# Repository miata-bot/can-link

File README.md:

# Underglow Sync Device

Very much work in progress software and hardware project built with [Kicad](https://www.kicad.org/) for hardware, and C and [Lua](https://www.lua.org) for software. See [The requirements doc](Requirements.md) for the guts of the project.

## TLDR

Here's a [Twitter thread](https://twitter.com/pressy4pie/status/1504309482054029315) showing a demo of the ECU integration.
[video link](https://video.twimg.com/ext_tw_video/1504309386151301125/pu/vid/720x1280/zwIcUEVZBSSQAASE.mp4?tag=12).

Here's a [Twitter thread](https://twitter.com/pressy4pie/status/1506779115122139137) showing a demo of the GPS and companion application. [video link](https://video.twimg.com/ext_tw_video/1506778163891740673/pu/vid/720x1630/oxYdaMkSowD5uJmU.mp4?tag=12).

I've written up a few posts on the progress of the project

* [Original hardware design](https://cone.codes/posts/can-link/)
* [Short post on using PWM to drive LEDS](https://cone.codes/posts/nerves-pwm/)
* [Hardware redesign](https://cone.codes/posts/can-link-pt-2/)
* [Hardware reredesign](https://cone.codes/posts/can-link-pt-3/)
* [Hardware rereredesign](https://cone.codes/posts/can-link-pt-4/)
* [Designing a Development test board](https://cone.codes/posts/imx6-devboard/)

## Description

This README acts as a root for all the jillion projects contained within the repo. There is no inherit relationship between any folders. Some are Elixir, some are flutter, etc. One day clean it up. Too much proof of concepting going on right now.

| Folder Name | Description | Language | License |
| ------------| ----------- | -------- | ------- |
| [hardware](hardware/README.md) | Main hardware designs. Contains schematics, layouts, boms, manufacturing gerbers etc. | KiCad | Creative Commons |
| [firmware](firmware/README.md) | Main Firmware projects. | C++ | MIT |

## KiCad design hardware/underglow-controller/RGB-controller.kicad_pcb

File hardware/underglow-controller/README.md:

# RGB Controller

Device designed to control RGB LEDs and syncronize across multiple nodes
via packet radio.

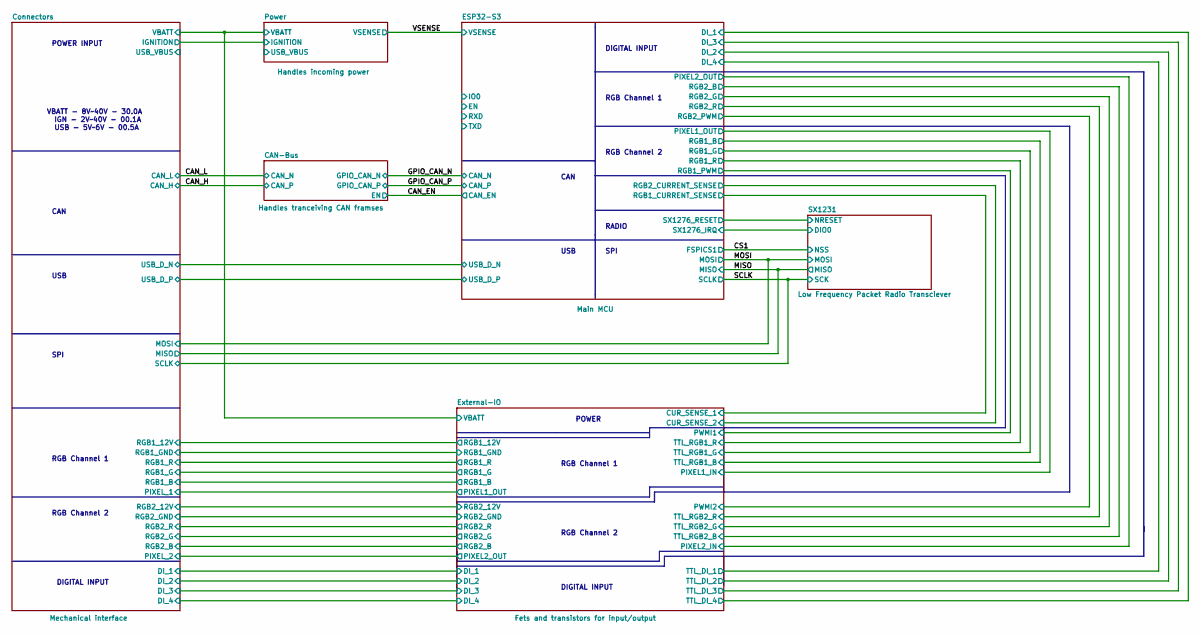
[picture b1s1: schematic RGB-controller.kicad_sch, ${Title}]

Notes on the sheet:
CAN
RGB Channel 2
USB
RGB Channel 1
SPI
DIGITAL INPUT
POWER INPUT
VBATT - 8V~40V - 30.0A IGN - 2V~40V - 00.1A USB - 5V~6V - 00.5A
POWER
RADIO

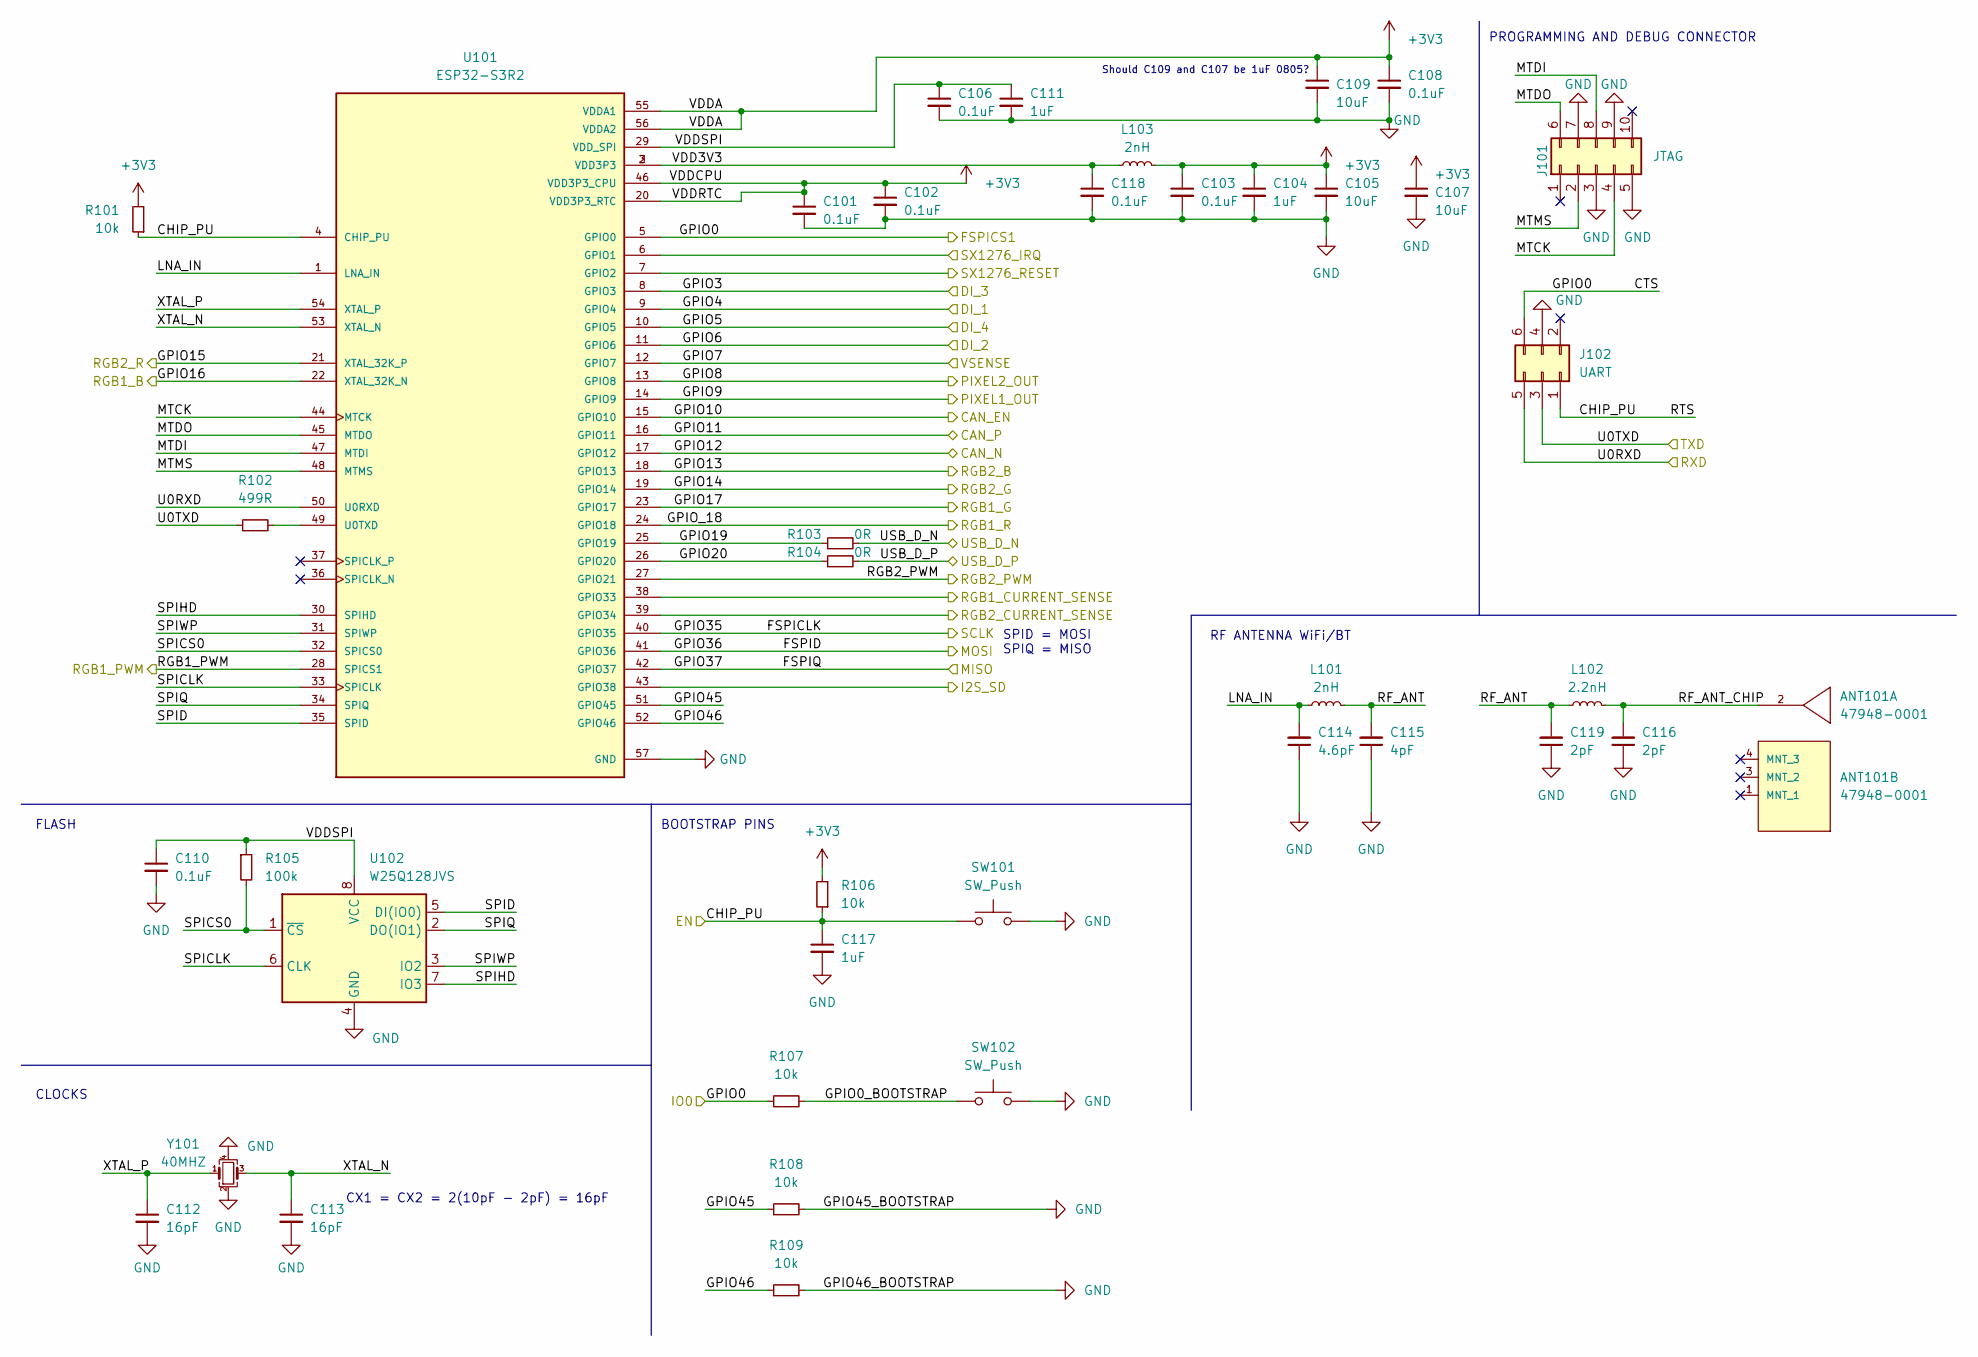
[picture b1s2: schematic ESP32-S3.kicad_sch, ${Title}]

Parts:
ANT101: 47948-0001; Molex-47948-0001-0-0-0; Digikey WM4893CT-ND
C101, C102, C103, C106, C108, C110, C118: 0.1uF; C_0402_1005Metric; Digikey CGA2B1X7R1C104M050BC
C104, C111, C117: 1uF; C_0402_1005Metric; Digikey CGA2B1X7T0G105M050BC
C105, C107, C109: 10uF; C_0805_2012Metric; Digikey GRT21BC81A106KE01L
C112, C113: 16pF; C_0402_1005Metric; Digikey GCM1555C1H160JA16D
C114: 4.6pF; C_0402_1005Metric; Digikey CBR04C469B5GAC
C115: 4pF; C_0402_1005Metric; Digikey UMK105UJ040CV-F
C116, C119: 2pF; C_0402_1005Metric; Digikey UMK105CK020CVHF
J101: JTAG; Tag-Connect_TC2050-IDC-FP_2x05_P1.27mm_Vertical; Digikey TC2050-IDC
J102: UART; Tag-Connect_TC2030-IDC-FP_2x03_P1.27mm_Vertical; Digikey TC2030-IDC
L101, L103: 2nH; L_0402_1005Metric; Digikey LQG15HN2N0C02D
L102: 2.2nH; L_0402_1005Metric; Digikey L-07C2N2SV6T
R101, R106, R107, R108, R109: 10k; R_0402_1005Metric; Digikey RMCF0402JT10K0
R102: 499R; R_0402_1005Metric; Digikey RMCF0402FT499R
R103, R104: 0R; R_0402_1005Metric; Digikey RC0402JR-070RP
R105: 100k; R_0402_1005Metric; Digikey RNCF0402DTE100K
SW101, SW102: SW_Push; SW_RS-032G05A3-SMRT; Digikey RS032G05A3SMRT
U101: ESP32-S3R2; QFN-56; Digikey ESP32-S3
U102: W25Q128JVS; SOIC-8W_5.3x5.3mm_P1.27mm; Digikey W25Q128JVS
Y101: 40MHZ; Crystal_SMD_3225-4Pin_3.2x2.5mm; Digikey ECS-400-10-37B2-CKY-TR

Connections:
+3V3: C101.1, C102.1, C103.1, C104.1, C105.1, C107.1, C108.1, C109.1, L103.2, R101.2, R106.2, U101.20 (VDD3P3_RTC), U101.46 (VDD3P3_CPU), U101.55 (VDDA1), U101.56 (VDDA2); also elsewhere on the board
/CAN_EN: U101.15 (GPIO10); also elsewhere on the board
/CS1: J102.6, R107.1, U101.5 (GPIO0); also elsewhere on the board
/ESP32-S3/CHIP_PU: C117.1, J102.1, R101.1, R106.1, SW101.1, U101.4 (CHIP_PU)
/ESP32-S3/GPIO0_BOOTSTRAP: R107.2, SW102.1
/ESP32-S3/GPIO3: U101.8 (GPIO3); also elsewhere on the board
/ESP32-S3/GPIO4: U101.9 (GPIO4); also elsewhere on the board
/ESP32-S3/GPIO5: U101.10 (GPIO5); also elsewhere on the board
/ESP32-S3/GPIO6: U101.11 (GPIO6); also elsewhere on the board
/ESP32-S3/GPIO8: U101.13 (GPIO8); also elsewhere on the board
/ESP32-S3/GPIO9: U101.14 (GPIO9); also elsewhere on the board
/ESP32-S3/GPIO13: U101.18 (GPIO13); also elsewhere on the board
/ESP32-S3/GPIO14: U101.19 (GPIO14); also elsewhere on the board
/ESP32-S3/GPIO15: U101.21 (XTAL_32K_P); also elsewhere on the board
/ESP32-S3/GPIO16: U101.22 (XTAL_32K_N); also elsewhere on the board
/ESP32-S3/GPIO17: U101.23 (GPIO17); also elsewhere on the board
/ESP32-S3/GPIO19: R103.1, U101.25 (GPIO19)
/ESP32-S3/GPIO20: R104.1, U101.26 (GPIO20)
/ESP32-S3/GPIO45: R108.1, U101.51 (GPIO45)
/ESP32-S3/GPIO46: R109.1, U101.52 (GPIO46)
/ESP32-S3/GPIO_18: U101.24 (GPIO18); also elsewhere on the board
/ESP32-S3/I2S_SD: U101.43 (GPIO38)
/ESP32-S3/LNA_IN: C114.2, L101.1, U101.1 (LNA_IN)
/ESP32-S3/MTCK: J101.4, U101.44 (MTCK)
/ESP32-S3/MTDI: J101.8, U101.47 (MTDI)
/ESP32-S3/MTDO: J101.6, U101.45 (MTDO)
/ESP32-S3/MTMS: J101.2, U101.48 (MTMS)
/ESP32-S3/RF_ANT: C115.2, C119.2, L101.2, L102.1
/ESP32-S3/RF_ANT_CHIP: ANT101.2 (FEEDING_PAD), C116.2, L102.2
/ESP32-S3/RGB1_CURRENT_SENSE: U101.38 (GPIO33); also elsewhere on the board
/ESP32-S3/RGB1_PWM: U101.28 (SPICS1); also elsewhere on the board
/ESP32-S3/RGB2_CURRENT_SENSE: U101.39 (GPIO34); also elsewhere on the board
/ESP32-S3/RGB2_PWM: U101.27 (GPIO21); also elsewhere on the board
/ESP32-S3/SPICLK: U101.33 (SPICLK), U102.6 (CLK)
/ESP32-S3/SPICS0: R105.2, U101.32 (SPICS0), U102.1 (~CS)
/ESP32-S3/SPID: U101.35 (SPID), U102.5 (DI(IO0))
/ESP32-S3/SPIHD: U101.30 (SPIHD), U102.7 (IO3)
/ESP32-S3/SPIQ: U101.34 (SPIQ), U102.2 (DO(IO1))
/ESP32-S3/SPIWP: U101.31 (SPIWP), U102.3 (IO2)
/ESP32-S3/U0RXD: J102.5, U101.50 (U0RXD)
/ESP32-S3/U0TXD: J102.3, R102.1
/ESP32-S3/USB_D_N: R103.2
/ESP32-S3/USB_D_P: R104.2
/ESP32-S3/VDD3V3: C118.1, L103.1, U101.2 (VDD3P3), U101.3 (VDD3P3)
/ESP32-S3/VDDSPI: C106.1, C110.1, C111.1, R105.1, U101.29 (VDD_SPI), U102.8 (VCC)
/ESP32-S3/XTAL_N: C113.1, U101.53 (XTAL_N), Y101.3
/ESP32-S3/XTAL_P: C112.1, U101.54 (XTAL_P), Y101.1
/GPIO_CAN_N: U101.17 (GPIO12); also elsewhere on the board
/GPIO_CAN_P: U101.16 (GPIO11); also elsewhere on the board
/MISO: U101.42 (GPIO37); also elsewhere on the board
/MOSI: U101.41 (GPIO36); also elsewhere on the board
/SCLK: U101.40 (GPIO35); also elsewhere on the board
/SX1231/DIO0: U101.6 (GPIO1); also elsewhere on the board
/SX1231/NRESET: U101.7 (GPIO2); also elsewhere on the board
/VSENSE: U101.12 (GPIO7); also elsewhere on the board
GND: C101.2, C102.2, C103.2, C104.2, C105.2, C106.2, C107.2, C108.2, C109.2, C110.2, C111.2, C112.2, C113.2, C114.1, C115.1, C116.1, C117.2, C118.2, C119.1, J101.3, J101.5, J101.7, J101.9, J102.4, R108.2, R109.2, SW101.2, SW102.2, U101.57 (GND), U102.4 (GND), Y101.2, Y101.4; also elsewhere on the board
unnamed: R102.2, U101.49 (U0TXD)

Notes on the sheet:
CX1 = CX2 = 2(10pF - 2pF) = 16pF
SPID = MOSI SPIQ = MISO
BOOTSTRAP PINS
FLASH
CLOCKS
PROGRAMMING AND DEBUG CONNECTOR
RF ANTENNA WiFi/BT
Should C109 and C107 be 1uF 0805?

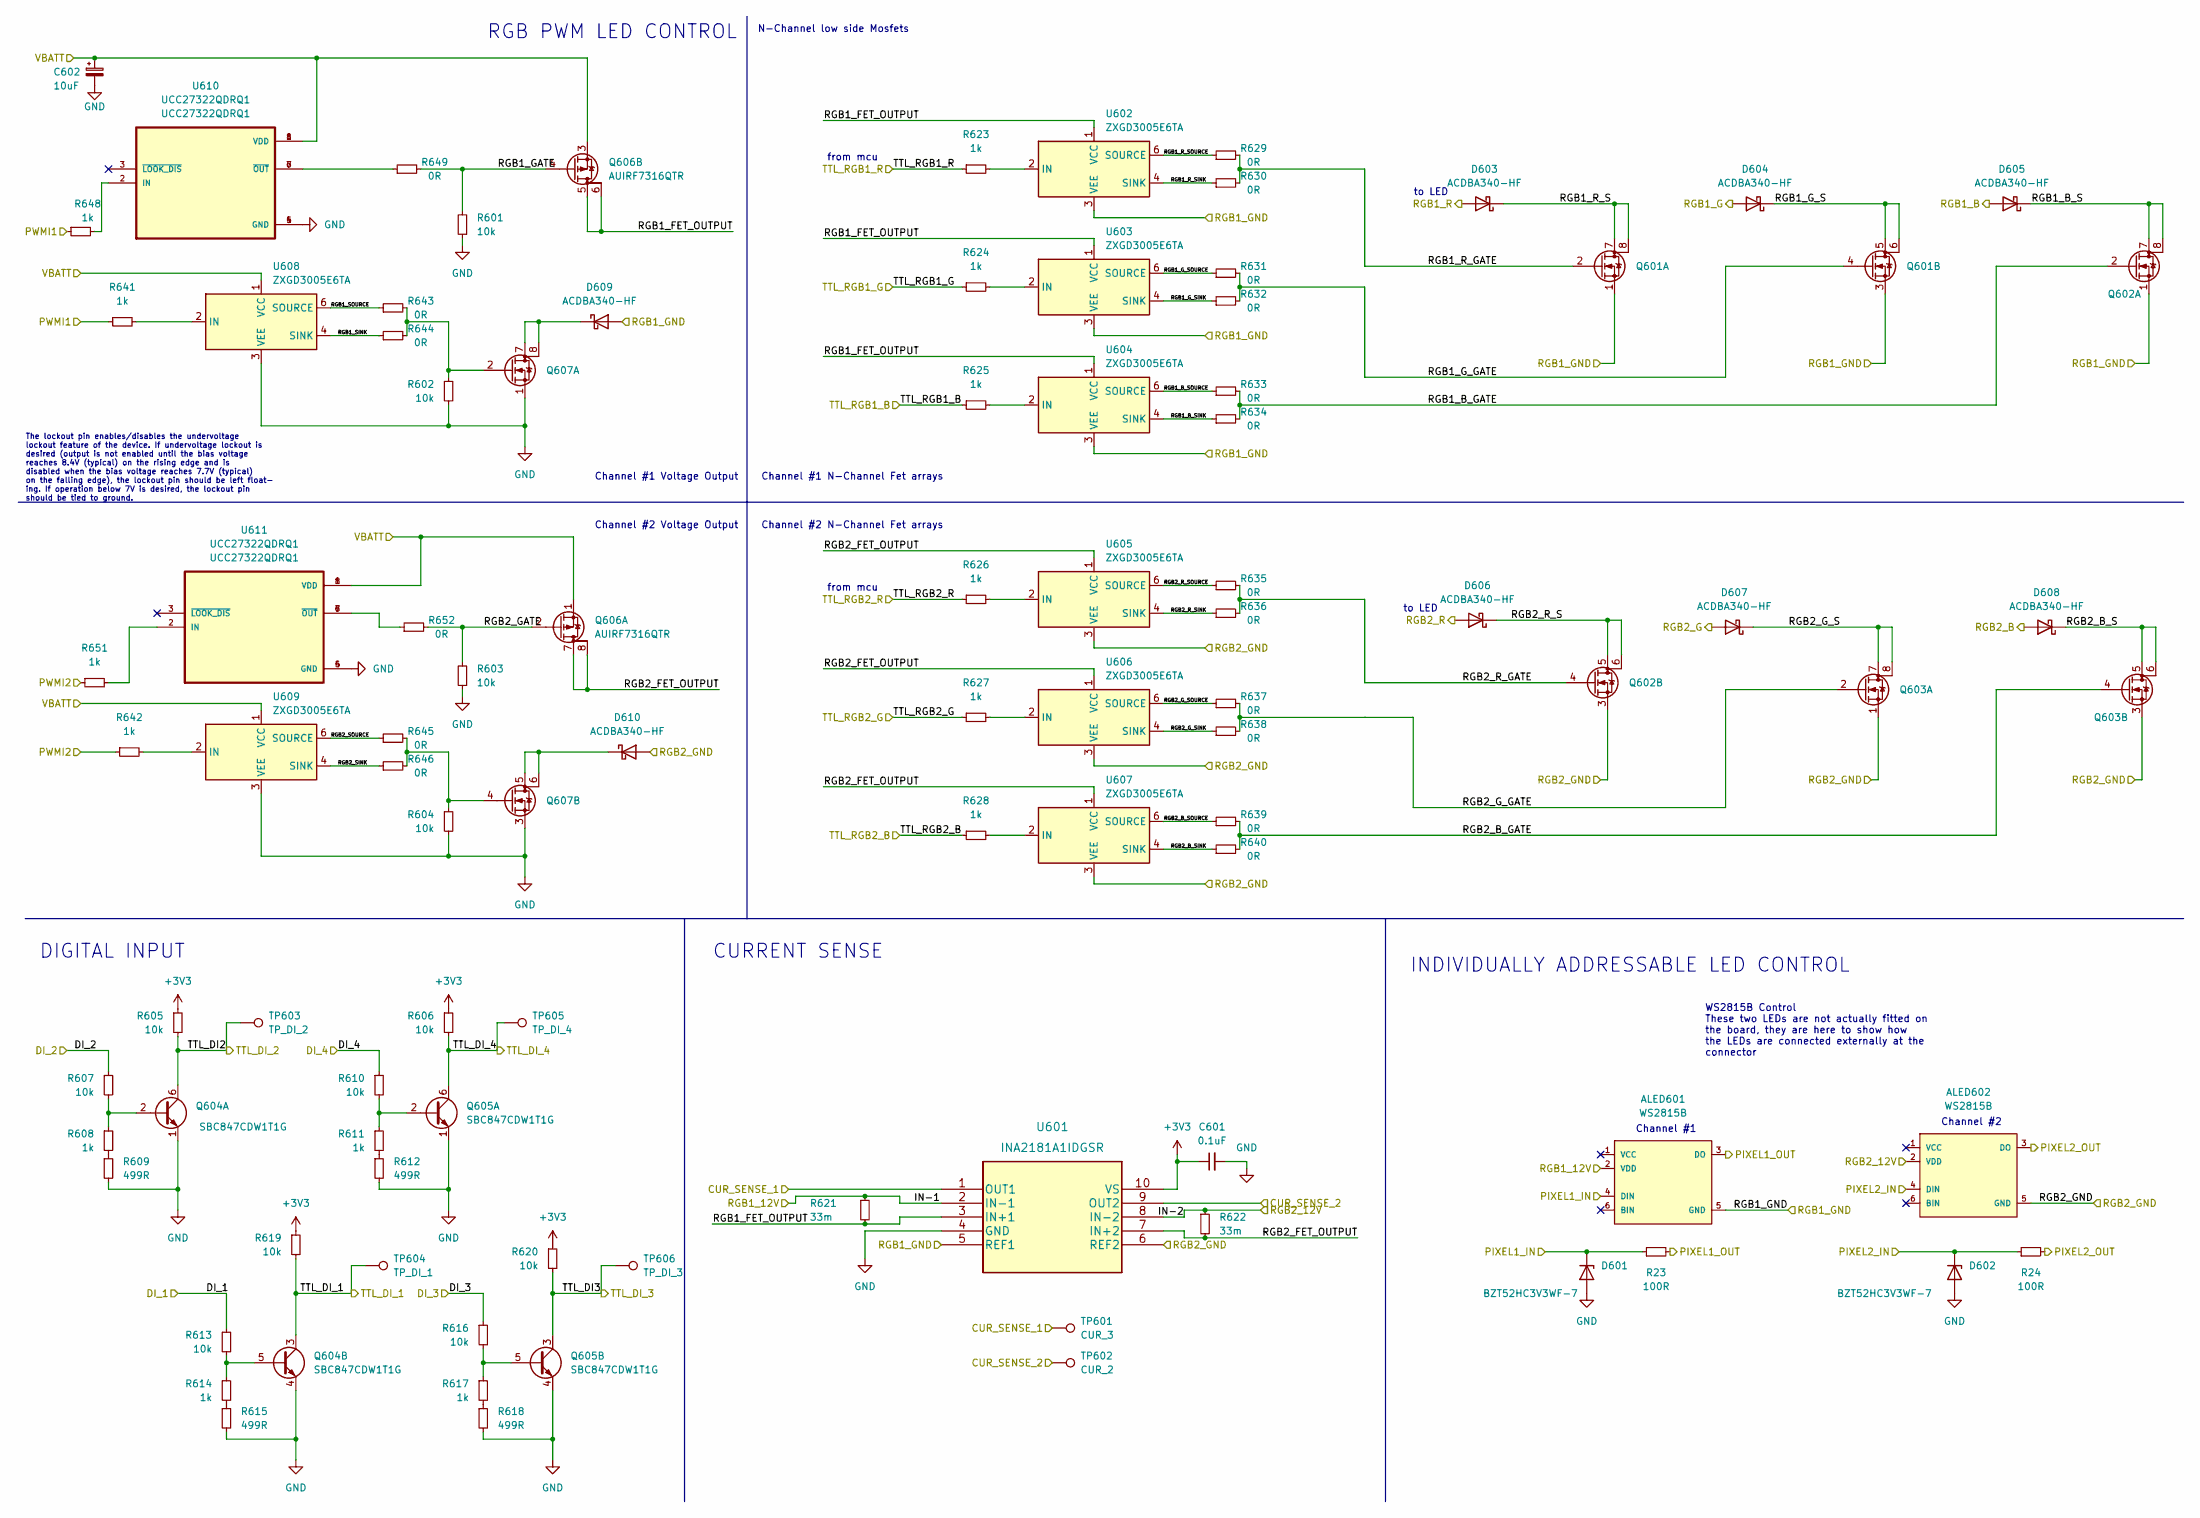
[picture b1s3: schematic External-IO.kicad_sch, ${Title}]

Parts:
ALED601, ALED602: WS2815B; worldsemi-WS2815B-*; Digikey 47948-0001
C601: 0.1uF; C_0402_1005Metric; Digikey CGA2B1X7R1C104M050BC
C602: 10uF; CP_Elec_5x5.9; Digikey 106AXZ035M
D601, D602: BZT52HC3V3WF-7; D_SOD-123F; Digikey BZT52HC3V3WF-7
D603, D604, D605, D606, D607, D608, D609, D610: ACDBA340-HF; D_SMA; Digikey ACDBA340-HF
Q601, Q602, Q603, Q607: SQ4282EY-T1_BE3; SO-8_3.9x4.9mm_P1.27mm; Digikey SQ4282EY-T1_BE3
Q604, Q605: SBC847CDW1T1G; SOT-363_SC-70-6; Digikey SBC847CDW1T1G
Q606: AUIRF7316QTR; SO-8_3.9x4.9mm_P1.27mm; Digikey AUIRF7316QTR
R23, R24: 100R; R_2512_6332Metric
R601, R602, R603, R604: 10k; R_0805_2012Metric; Digikey RNCP0805FTD10K0
R605, R606, R607, R610, R613, R616, R619, R620: 10k; R_0402_1005Metric; Digikey RMCF0402JT10K0
R608, R611, R614, R617, R623, R624, R625, R626, R627, R628, R641, R642, R648, R651: 1k; R_0402_1005Metric; Digikey RMCF0402FT1K00
R609, R612, R615, R618: 499R; R_0402_1005Metric; Digikey RMCF0402FT499R
R621, R622: 33m; R_2512_6332Metric; Digikey CSM2512FT33L0
R629, R630, R631, R632, R633, R634, R635, R636, R637, R638, R639, R640, R643, R644, R645, R646, R649, R652: 0R; R_0805_2012Metric; Digikey RMCF0805ZT0R00
TP601: CUR_3; TestPoint_Pad_D1.0mm
TP602: CUR_2; TestPoint_Pad_D1.0mm
TP603: TP_DI_2; TestPoint_Pad_D1.0mm
TP604: TP_DI_1; TestPoint_Pad_D1.0mm
TP605: TP_DI_4; TestPoint_Pad_D1.0mm
TP606: TP_DI_3; TestPoint_Pad_D1.0mm
U601: INA2181A1IDGSR; VSSOP-10_3x3mm_P0.5mm; Digikey INA2181A1IDGSR
U602, U603, U604, U605, U606, U607, U608, U609: ZXGD3005E6TA; SOT-23-6; Digikey ZXGD3005E6TA
U610, U611: UCC27322QDRQ1; SOIC127P600X175-8N; Digikey UCC27322QDRQ1

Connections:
+3V3: C601.1, R605.1, R606.1, R619.1, R620.1, U601.10 (VS); also elsewhere on the board
/Connectors/DI_1: R613.1; also elsewhere on the board
/Connectors/DI_2: R607.1; also elsewhere on the board
/Connectors/DI_3: R616.1; also elsewhere on the board
/Connectors/DI_4: R610.1; also elsewhere on the board
/Connectors/PIXEL_1: ALED601.3 (DO), R23.2; also elsewhere on the board
/Connectors/PIXEL_2: ALED602.3 (DO), R24.2; also elsewhere on the board
/Connectors/RGB1_12V: ALED601.2 (VDD), R621.1, U601.2 (IN-1); also elsewhere on the board
/Connectors/RGB1_B: D605.2 (A); also elsewhere on the board
/Connectors/RGB1_G: D604.2 (A); also elsewhere on the board
/Connectors/RGB1_GND: ALED601.5 (GND), D609.2 (A), Q601.1 (S), Q601.3 (S), Q602.1 (S), U601.5 (REF1), U602.3 (VEE), U603.3 (VEE), U604.3 (VEE); also elsewhere on the board
/Connectors/RGB1_R: D603.2 (A); also elsewhere on the board
/Connectors/RGB2_12V: ALED602.2 (VDD), R622.1, U601.8 (IN-2); also elsewhere on the board
/Connectors/RGB2_B: D608.2 (A); also elsewhere on the board
/Connectors/RGB2_G: D607.2 (A); also elsewhere on the board
/Connectors/RGB2_GND: ALED602.5 (GND), D610.2 (A), Q602.3 (S), Q603.1 (S), Q603.3 (S), U601.6 (REF2), U605.3 (VEE), U606.3 (VEE), U607.3 (VEE); also elsewhere on the board
/Connectors/RGB2_R: D606.2 (A); also elsewhere on the board
/Connectors/VBATT: C602.1, Q606.1 (S), Q606.3 (S), U608.1 (VCC), U609.1 (VCC), U610.1 (VDD), U610.8 (VDD), U611.1 (VDD), U611.8 (VDD); also elsewhere on the board
/ESP32-S3/GPIO3: Q605.3 (C509), R620.2, TP606.1; also elsewhere on the board
/ESP32-S3/GPIO4: Q605.6 (C1), R606.2, TP605.1; also elsewhere on the board
/ESP32-S3/GPIO5: Q604.3 (C509), R619.2, TP604.1; also elsewhere on the board
/ESP32-S3/GPIO6: Q604.6 (C1), R605.2, TP603.1; also elsewhere on the board
/ESP32-S3/GPIO8: ALED602.4 (DIN), D602.1 (K), R24.1; also elsewhere on the board
/ESP32-S3/GPIO9: ALED601.4 (DIN), D601.1 (K), R23.1; also elsewhere on the board
/ESP32-S3/GPIO13: R628.1; also elsewhere on the board
/ESP32-S3/GPIO14: R627.1; also elsewhere on the board
/ESP32-S3/GPIO15: R626.1; also elsewhere on the board
/ESP32-S3/GPIO16: R625.1; also elsewhere on the board
/ESP32-S3/GPIO17: R624.1; also elsewhere on the board
/ESP32-S3/GPIO_18: R623.1; also elsewhere on the board
/ESP32-S3/RGB1_CURRENT_SENSE: TP601.1, U601.1 (OUT1); also elsewhere on the board
/ESP32-S3/RGB1_PWM: R641.1, R648.1; also elsewhere on the board
/ESP32-S3/RGB2_CURRENT_SENSE: TP602.1, U601.9 (OUT2); also elsewhere on the board
/ESP32-S3/RGB2_PWM: R642.1, R651.1; also elsewhere on the board
/External-IO/RGB1_B_GATE: Q602.2 (G), R633.2, R634.2
/External-IO/RGB1_B_S: D605.1 (K), Q602.7 (D), Q602.8 (D)
/External-IO/RGB1_B_SINK: R634.1, U604.4 (SINK)
/External-IO/RGB1_B_SOURCE: R633.1, U604.6 (SOURCE)
/External-IO/RGB1_FET_OUTPUT: Q606.5 (D), Q606.6 (G), R621.2, U601.3 (IN+1), U602.1 (VCC), U603.1 (VCC), U604.1 (VCC)
/External-IO/RGB1_GATE: Q606.4 (G), R601.2, R649.2
/External-IO/RGB1_G_GATE: Q601.4 (G), R631.2, R632.2
/External-IO/RGB1_G_S: D604.1 (K), Q601.5 (D), Q601.6 (D)
/External-IO/RGB1_G_SINK: R632.1, U603.4 (SINK)
/External-IO/RGB1_G_SOURCE: R631.1, U603.6 (SOURCE)
/External-IO/RGB1_R_GATE: Q601.2 (G), R629.2, R630.2
/External-IO/RGB1_R_S: D603.1 (K), Q601.7 (D), Q601.8 (D)
/External-IO/RGB1_R_SINK: R630.1, U602.4 (SINK)
/External-IO/RGB1_R_SOURCE: R629.1, U602.6 (SOURCE)
/External-IO/RGB1_SINK: R644.1, U608.4 (SINK)
/External-IO/RGB1_SOURCE: R643.1, U608.6 (SOURCE)
/External-IO/RGB2_B_GATE: Q603.4 (G), R639.2, R640.2
/External-IO/RGB2_B_S: D608.1 (K), Q603.5 (D), Q603.6 (D)
/External-IO/RGB2_B_SINK: R640.1, U607.4 (SINK)
/External-IO/RGB2_B_SOURCE: R639.1, U607.6 (SOURCE)
/External-IO/RGB2_FET_OUTPUT: Q606.7 (D), Q606.8 (G), R622.2, U601.7 (IN+2), U605.1 (VCC), U606.1 (VCC), U607.1 (VCC)
/External-IO/RGB2_GATE: Q606.2 (G), R603.2, R652.2
/External-IO/RGB2_G_GATE: Q603.2 (G), R637.2, R638.2
/External-IO/RGB2_G_S: D607.1 (K), Q603.7 (D), Q603.8 (D)
/External-IO/RGB2_G_SINK: R638.1, U606.4 (SINK)
/External-IO/RGB2_G_SOURCE: R637.1, U606.6 (SOURCE)
/External-IO/RGB2_R_GATE: Q602.4 (G), R635.2, R636.2
/External-IO/RGB2_R_S: D606.1 (K), Q602.5 (D), Q602.6 (D)
/External-IO/RGB2_R_SINK: R636.1, U605.4 (SINK)
/External-IO/RGB2_R_SOURCE: R635.1, U605.6 (SOURCE)
/External-IO/RGB2_SINK: R646.1, U609.4 (SINK)
/External-IO/RGB2_SOURCE: R645.1, U609.6 (SOURCE)
GND: C601.2, C602.2, D601.2 (A), D602.2 (A), Q604.1 (E1), Q604.4 (E2), Q605.1 (E1), Q605.4 (E2), Q607.1 (S), Q607.3 (S), R601.1, R602.2, R603.1, R604.2, R609.2, R612.2, R615.2, R618.2, U601.4 (GND), U608.3 (VEE), U609.3 (VEE), U610.4 (GND), U610.5 (GND), U611.4 (GND), U611.5 (GND); also elsewhere on the board
unnamed: D609.1 (K), Q607.7 (D), Q607.8 (D)
unnamed: D610.1 (K), Q607.5 (D), Q607.6 (D)
unnamed: Q604.2 (B1), R607.2, R608.1
unnamed: Q604.5 (B2), R613.2, R614.1
unnamed: Q605.2 (B1), R610.2, R611.1
unnamed: Q605.5 (B2), R616.2, R617.1
unnamed: Q607.2 (G), R602.1, R643.2, R644.2
unnamed: Q607.4 (G), R604.1, R645.2, R646.2
unnamed: R608.2, R609.1
unnamed: R611.2, R612.1
unnamed: R614.2, R615.1
unnamed: R617.2, R618.1
unnamed: R623.2, U602.2 (IN)
unnamed: R624.2, U603.2 (IN)
unnamed: R625.2, U604.2 (IN)
unnamed: R626.2, U605.2 (IN)
unnamed: R627.2, U606.2 (IN)
unnamed: R628.2, U607.2 (IN)
unnamed: R641.2, U608.2 (IN)
unnamed: R642.2, U609.2 (IN)
unnamed: R648.2, U610.2 (IN)
unnamed: R649.1, U610.6 (~OUT), U610.7 (~OUT)
unnamed: R651.2, U611.2 (IN)
unnamed: R652.1, U611.6 (~OUT), U611.7 (~OUT)

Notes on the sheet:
to LED
Channel #2
DIGITAL INPUT
from mcu
Channel #1 N-Channel Fet arrays
The lockout pin enables/disables the undervoltage lockout feature of the device. If undervoltage lockout is desired (output is not enabled until the bias voltage reaches 8.4V (typical) on the rising edge and is disabled when the bias voltage reaches 7.7V (typical) on the falling edge), the lockout 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
WS2815B Control These two LEDs are not actually fitted on the board, they are here to show how the LEDs are connected externally at the connector
RGB PWM LED CONTROL
Channel #2 Voltage Output
Channel #1 Voltage Output
CURRENT SENSE
N-Channel low side Mosfets
Channel #2 N-Channel Fet arrays
INDIVIDUALLY ADDRESSABLE LED CONTROL
Channel #1

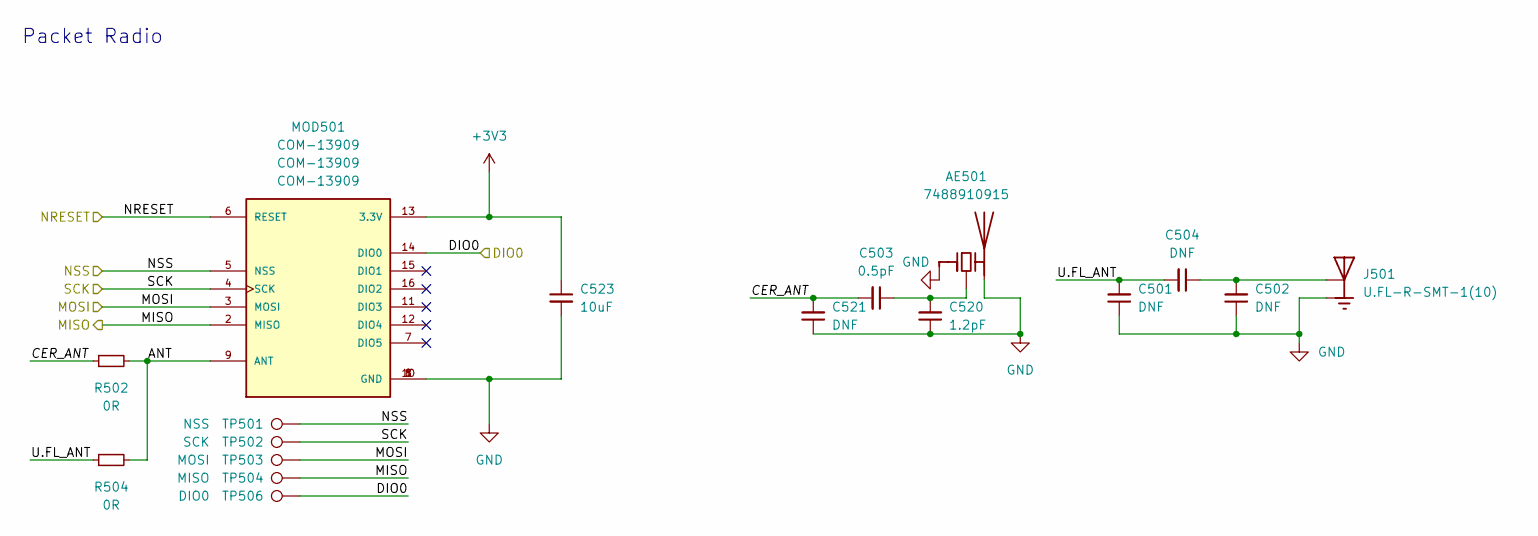
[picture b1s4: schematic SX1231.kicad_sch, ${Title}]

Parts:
AE501: 7488910915; Digikey 7488910915
C501, C502, C504, C521: DNF; C_0402_1005Metric
C503: 0.5pF; C_0402_1005Metric; Digikey C0402C508D3GAC7867
C520: 1.2pF; C_0402_1005Metric; Digikey C0402C129D3GAC7867
C523: 10uF; C_0805_2012Metric; Digikey GRT21BC81A106KE01L
J501: U.FL-R-SMT-1(10); HRS_U.FL-R-SMT-1(10); Digikey U.FL-R-SMT-1(10)
MOD501: COM-13909; HOPERF_RFM9XW_SMD; MPN2 COM-13909; Digikey COM-13909
R502, R504: 0R; R_0402_1005Metric; Digikey RC0402JR-070RP
TP501: NSS; TestPoint_Pad_D1.0mm
TP502: SCK; TestPoint_Pad_D1.0mm
TP503: MOSI; TestPoint_Pad_D1.0mm
TP504: MISO; TestPoint_Pad_D1.0mm
TP506: DIO0; TestPoint_Pad_D1.0mm

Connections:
+3V3: C523.1, MOD501.13 (3.3V); also elsewhere on the board
/CS1: MOD501.5 (NSS), TP501.1; also elsewhere on the board
/MISO: MOD501.2 (MISO), TP504.1; also elsewhere on the board
/MOSI: MOD501.3 (MOSI), TP503.1; also elsewhere on the board
/SCLK: MOD501.4 (SCK), TP502.1; also elsewhere on the board
/SX1231/ANT: MOD501.9 (ANT), R502.2, R504.2
/SX1231/CER_ANT: C503.2, C521.2, R502.1
/SX1231/DIO0: MOD501.14 (DIO0), TP506.1; also elsewhere on the board
/SX1231/NRESET: MOD501.6 (RESET); also elsewhere on the board
/SX1231/U.FL_ANT: C501.2, C504.2, R504.1
GND: AE501.1 (PCB_Trace), AE501.2 (PCB_Trace), C501.1, C502.1, C520.1, C521.1, C523.2, J501.1, J501.3, MOD501.1 (GND), MOD501.8 (GND), MOD501.10 (GND); also elsewhere on the board
unnamed: AE501.3 (FEED), C503.1, C520.2
unnamed: C502.2, C504.1, J501.2

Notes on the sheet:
Packet Radio

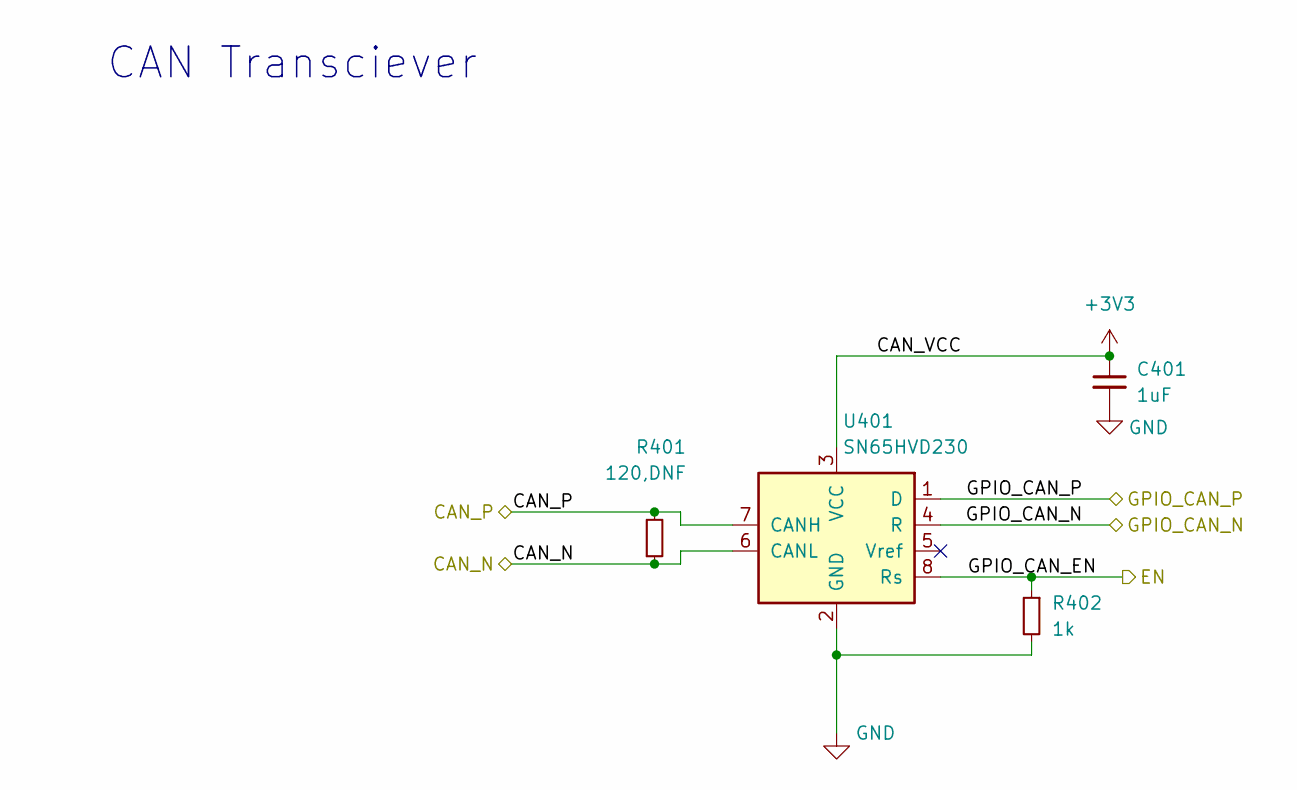
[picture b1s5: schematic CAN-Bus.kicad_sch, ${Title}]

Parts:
C401: 1uF; C_0402_1005Metric; Digikey CGA2B1X7T0G105M050BC
R401: 120,DNF; R_0805_2012Metric; Digikey RMCF0805JT120R
R402: 1k; R_0402_1005Metric; Digikey RMCF0402FT1K00
U401: SN65HVD230; SOIC-8_3.9x4.9mm_P1.27mm; Digikey SN65HVD230D

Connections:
+3V3: C401.1, U401.3 (VCC); also elsewhere on the board
/CAN_EN: R402.1, U401.8 (Rs); also elsewhere on the board
/CAN_H: R401.2, U401.7 (CANH); also elsewhere on the board
/CAN_L: R401.1, U401.6 (CANL); also elsewhere on the board
/GPIO_CAN_N: U401.4 (R); also elsewhere on the board
/GPIO_CAN_P: U401.1 (D); also elsewhere on the board
GND: C401.2, R402.2, U401.2 (GND); also elsewhere on the board

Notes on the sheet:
CAN Transciever

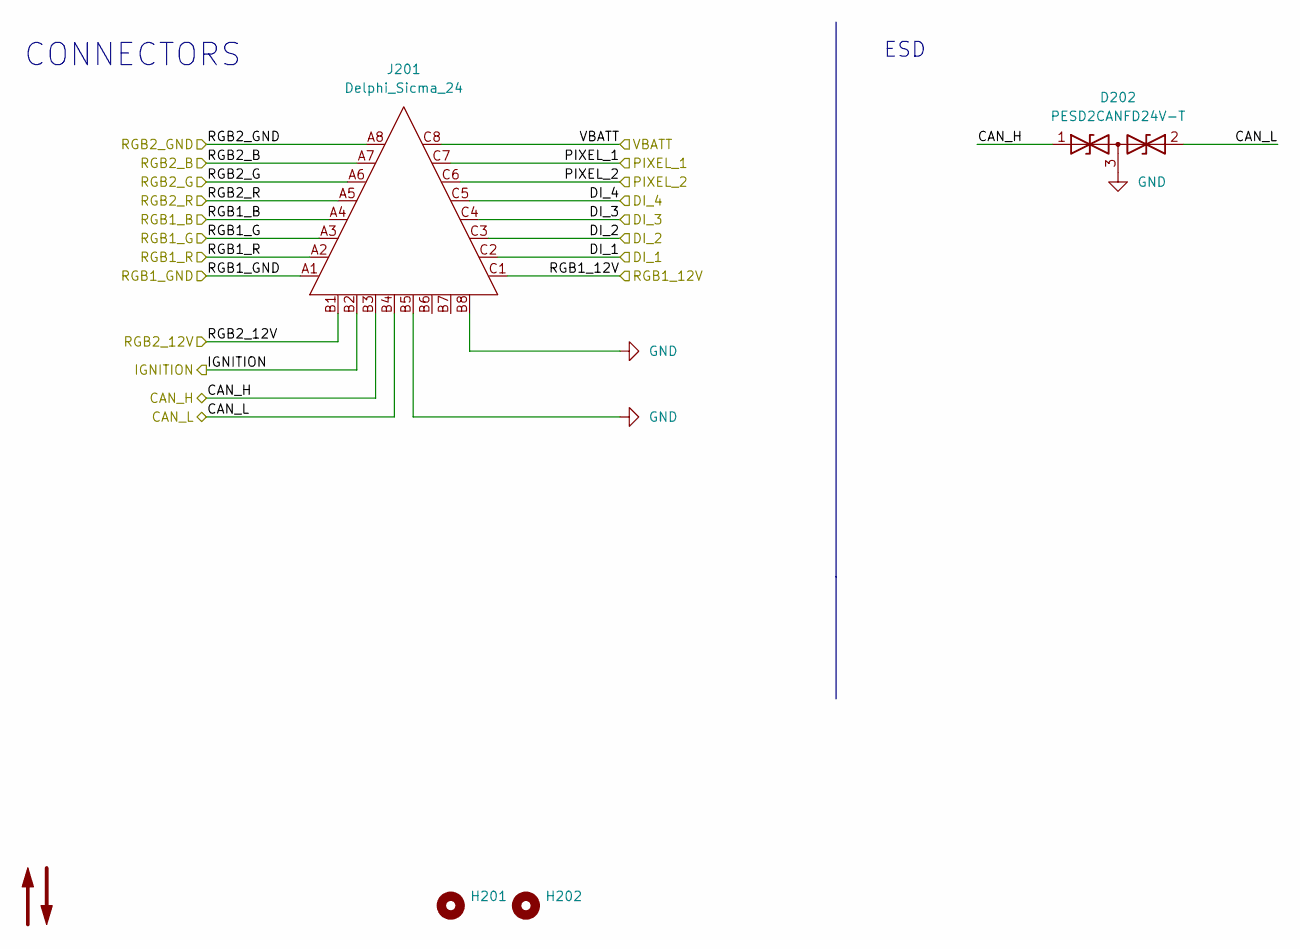
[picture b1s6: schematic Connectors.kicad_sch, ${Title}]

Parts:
D202: PESD2CANFD24V-T; SOT-23; Digikey PESD2CANFD24V-T
H201, H202: MountingHole_Pad; MountingHole_2.7mm_M2.5
J201: Delphi_Sicma_24; Delphi_Sicma_24_Black

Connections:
/CAN_H: D202.1 (A1), J201.B3; also elsewhere on the board
/CAN_L: D202.2 (A2), J201.B4; also elsewhere on the board
/Connectors/DI_1: J201.C2; also elsewhere on the board
/Connectors/DI_2: J201.C3; also elsewhere on the board
/Connectors/DI_3: J201.C4; also elsewhere on the board
/Connectors/DI_4: J201.C5; also elsewhere on the board
/Connectors/IGNITION: J201.B2; also elsewhere on the board
/Connectors/PIXEL_1: J201.C7; also elsewhere on the board
/Connectors/PIXEL_2: J201.C6; also elsewhere on the board
/Connectors/RGB1_12V: J201.C1; also elsewhere on the board
/Connectors/RGB1_B: J201.A4; also elsewhere on the board
/Connectors/RGB1_G: J201.A3; also elsewhere on the board
/Connectors/RGB1_GND: J201.A1; also elsewhere on the board
/Connectors/RGB1_R: J201.A2; also elsewhere on the board
/Connectors/RGB2_12V: J201.B1; also elsewhere on the board
/Connectors/RGB2_B: J201.A7; also elsewhere on the board
/Connectors/RGB2_G: J201.A6; also elsewhere on the board
/Connectors/RGB2_GND: J201.A8; also elsewhere on the board
/Connectors/RGB2_R: J201.A5; also elsewhere on the board
/Connectors/VBATT: J201.C8; also elsewhere on the board
GND: D202.3 (common), J201.B5, J201.B8; also elsewhere on the board

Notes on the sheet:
ESD
CONNECTORS

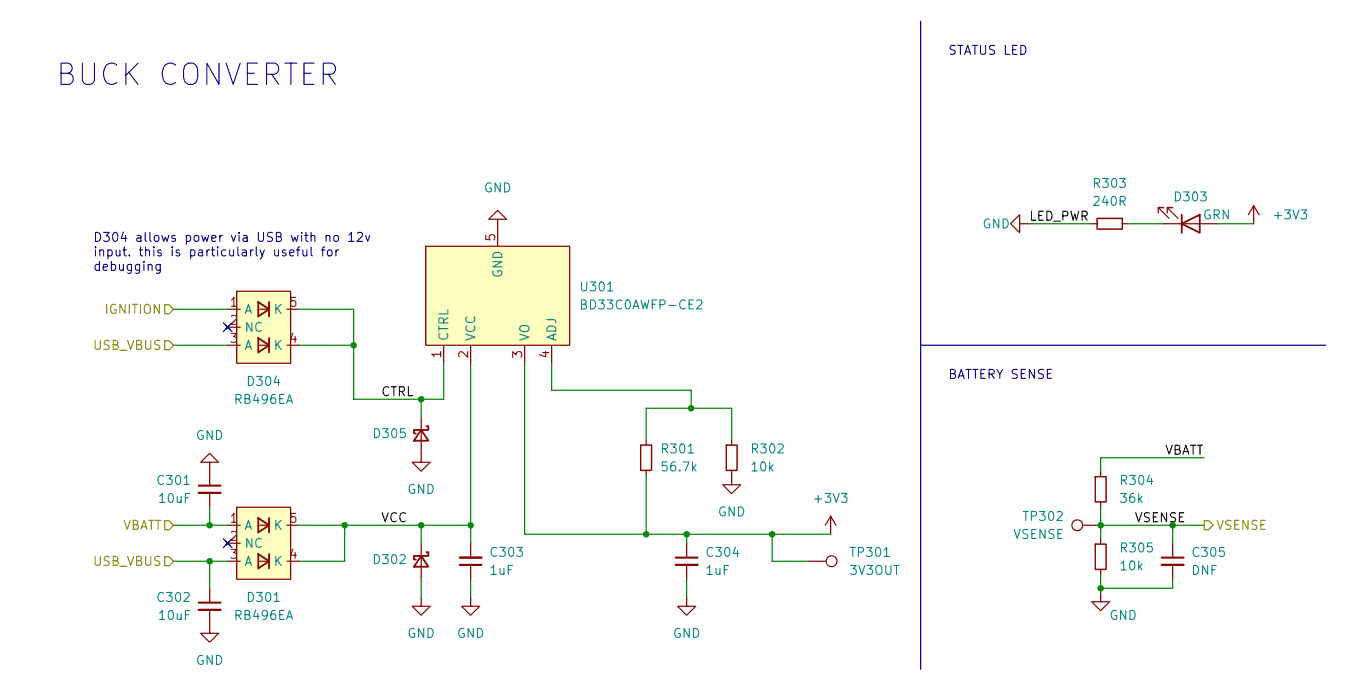
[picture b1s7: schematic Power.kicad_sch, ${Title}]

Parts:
C301, C302: 10uF; C_0805_2012Metric; Digikey GRT21BC81A106KE01L
C303, C304: 1uF; C_0805_2012Metric; Digikey CL21B105KOF4PNE
C305: DNF; C_0603_1608Metric
D301, D304: RB496EA; SOT-23-5; Digikey RB496EA
D302, D305: BYS10-45HE3_A/H; D_SMA; Digikey BYS10-45HE3_A/H
D303: GRN; LED_0603_1608Metric; Digikey LTST-C191KGKT
R301: 56.7k; R_0805_2012Metric; Digikey RMCF0805FT57K6
R302: 10k; R_0805_2012Metric; Digikey RNCP0805FTD10K0
R303: 240R; R_0603_1608Metric; Digikey RMCF0603JT240R
R304: 36k; R_0603_1608Metric
R305: 10k; R_0603_1608Metric
TP301: 3V3OUT; TestPoint_Pad_D1.0mm
TP302: VSENSE; TestPoint_Pad_D1.0mm
U301: BD33C0AWFP-CE2; Digikey BD33C0AWFP-CE2

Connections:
+3V3: C304.1, D303.2 (A), R301.2, TP301.1, U301.3 (VO); also elsewhere on the board
/Connectors/IGNITION: D304.1 (A); also elsewhere on the board
/Connectors/VBATT: C301.2, D301.1 (A), R304.1; also elsewhere on the board
/Power/CTRL: D304.4 (K), D304.5 (K), D305.1 (K), U301.1 (CTRL)
/Power/USB_VBUS: C302.1, D301.3 (A), D304.3 (A)
/Power/VCC: C303.2, D301.4 (K), D301.5 (K), D302.1 (K), U301.2 (VCC)
/VSENSE: C305.1, R304.2, R305.1, TP302.1; also elsewhere on the board
GND: C301.1, C302.2, C303.1, C304.2, C305.2, D302.2 (A), D305.2 (A), R302.2, R303.2, R305.2, U301.5 (GND); also elsewhere on the board
unnamed: D303.1 (K), R303.1
unnamed: R301.1, R302.1, U301.4 (ADJ)

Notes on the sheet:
STATUS LED
D304 allows power via USB with no 12v input. this is particularly useful for debugging
BUCK CONVERTER
BATTERY SENSE

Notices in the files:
firmware/rp2040_fw/src/main.c:
* Copyright (c) 2020 Raspberry Pi (Trading) Ltd.
* SPDX-License-Identifier: BSD-3-Clause
